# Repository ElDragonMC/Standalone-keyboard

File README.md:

# Standalone keyboard
This is my project for third week Half Life, a keyboard powered with a ESP32 connected to a power bank that uses a speaker to play 3 diferent sounds (acoustic, electric and organ). That's what makes it standalone!

I enjoyed very much making this project (specialy the PCB). For me, the most difficult part, was making the code so it can properly function.

# PCB Schematic:

# Some PCB Renders:

Front:

Back:

# Bill Of Materials

| Item | Qty | Supplier | Cost/item | Total Cost | link |
| --- | --- | --- | --- | --- | --- |
| PCB | 1 | JLCPCB | $5.00 | $5.00 | [JLCPCB](https://jlcpcb.com/) |
| Speaker | 1 | ElectroHobby | $1.66 | $1.66 | [ElectroHobby](https://www.electrohobby.es/sonido/305-altavoz-2w-28mm.html) |
| Amplifier | 1 | ElectroHobby | $2.78 | $2.78 | [ElectroHobby](https://www.electrohobby.es/sonido/984-max98357-amplificador-i2s.html) |
| Rotary Encoder | 1 | ElectroHobby | $1.28 | $1.28 | [ElectroHobby](https://www.electrohobby.es/entradassalidas/454-modulo-encoder-ky-040.html) |
| ESP32-S3-Zero | 1 | ElectroHobby | $5.00 | $5.00 | [ElectroHobby](https://www.electrohobby.es/esp32/957-esp32-c3-zero.html) |
| MPR121 | 1 | Amazon ES | $7.80 | $7.80 | [Amazon ES](	https://amzn.eu/d/0ajJMPyk) |
| 40x Blue Pin Header | ElectroHobby | $0.33 | $0.33 | [ElectroHobby](https://www.electrohobby.es/tiras-de-pines/236-tira-40-pin-macho-azul.html) |
| **Estimated total shipping** | **1** | — | — | **$3.49** | — |
| **Total Cost** | **1** | — | — | **$27.34** | — |

# Desing Process

I designed the PCB with KiCad (the only PCB design software i know how to use) following some parts from the starter guide to have a base idea. I wanted to make a case for it but i think it will look cooler to have it raw. A sleek black PCB will look very cool.

# How To Assemble

1. First grab the PCB and verify if it's clean and well-made.
2. Grab the ESP32, the MPR121 and the Amplifier and solder the pin headers. For the ESP32 it's two 9 pin header, for the MPR121, it's a 6 pin header and a 12 pin header and finaly for the amplifier it's two one pin header and a 7 pin header.
3. Weld the ESP32, the MPR121, the Amplifier, the JST connector for the speaker, the three switches and the rotary encoder to the PCB
4. There's two parts on the pack of the JST connector. One it's welded on the PCB. The other you have to solder it to the who cables of the speaker. **MAKE SURE THE RED WIRE GOES TO THE UPPER PART OF THE JST CONNECTOR**
5. Hot glue the speaker to the PCB

# How to upload the firmware

1. Open the Arduino IDE
2. Open **File → Preferences**. In **Additional Boards Manager URLs**, add:

   ~~~text
   https://espressif.github.io/arduino-esp32/package_esp32_index.json
   ~~~

3. Open **Tools → Board → Boards Manager**, search for esp32, and install **esp32 by Espressif Systems**.
4. Under **Tools → Board → esp32**, select **Waveshare ESP32-S3-Zero**.
5. Open **Sketch → Include Library → Manage Libraries**. Install this library:

   - Adafruit MPR121

   If Arduino asks to install dependencies, choose **Install All**.

6. Connect the ESP32 to the computer.
7. Open keyboard_code.ino and click Arduino's arrow-shaped **Upload** button to upload the firmware to the board.

# Controls

| Control (from left to right) | What it does |
| --- | --- |
| First button | Plays with the Acoustic sound |
| Second button | Plays with the Electric sound |
| Third button | Plays with the Organ sound |
| Rotary encoder | Control the volume |

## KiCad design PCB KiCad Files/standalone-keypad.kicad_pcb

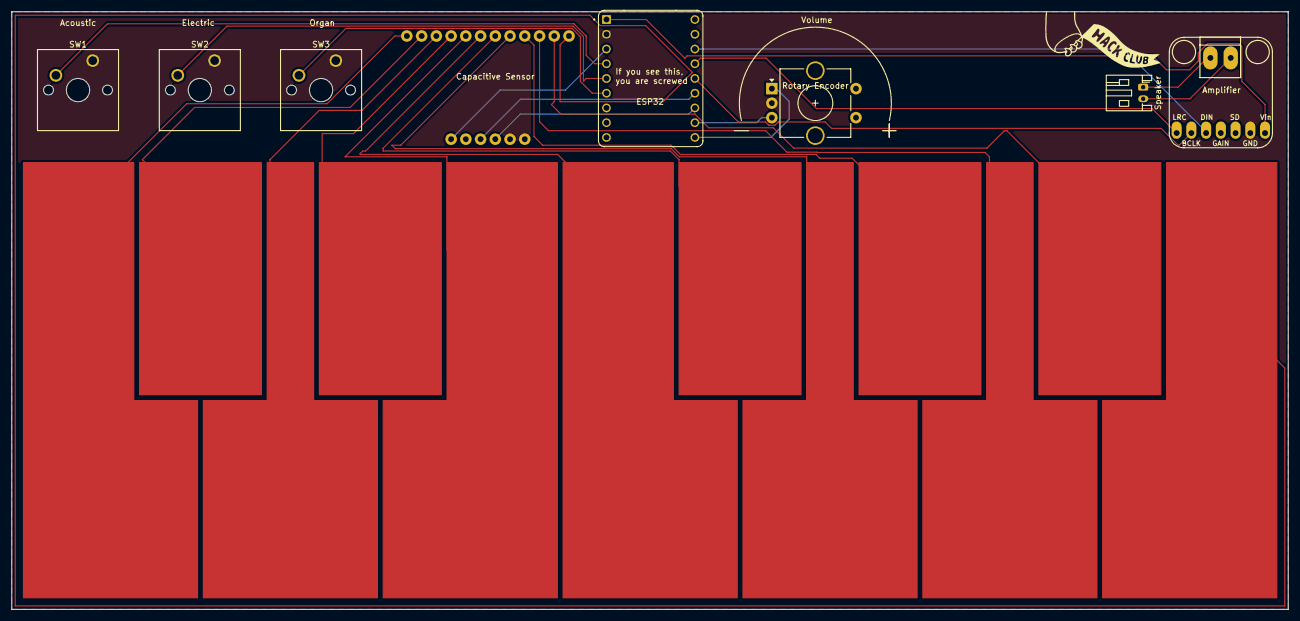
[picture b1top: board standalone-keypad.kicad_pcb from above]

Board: 2 copper layers, 220.0 x 103.0 mm, 9 parts (0 on the bottom side), 27 nets.

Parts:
Amplifier: adafruit-MAX98357 Amplifier; adafruit-MAX98357
Capacitive Sensor: MPR121QR2 Capacitive Sensor; MPR121
ESP32: Capacitive keys; Keyboard
Rotary Encoder: Volume Knob; RotaryEncoder_Alps_EC11E-Switch_Vertical_H20mm_CircularMoun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
SW1: Acoustic sound; SW_Cherry_MX_1.00u_PCB
SW2: Electric sound; SW_Cherry_MX_1.00u_PCB
SW3: Organ sound; SW_Cherry_MX_1.00u_PCB
Speaker: Speaker; JST_PH_S2B-PH-K_1x02_P2.00mm_Horizontal
U1: ESP32-S3-ZERO; MODULE_ESP32-S3-ZERO

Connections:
+3V3: Capacitive Sensor.1 (~IRQ), U1.3V3 (3V3(OUT))
+5V: Amplifier.1 (Vin), U1.5V
/ACOUSTIC: SW1.2, U1.1 (GP1)
/AUDIO DATA: Amplifier.5 (DIN), U1.13 (GP13)
/AUDIO TIMING 1: Amplifier.6 (BCLK), U1.11 (GP11)
/AUDIO TIMING 2: Amplifier.7 (LRC), U1.12 (GP12)
/DO: Capacitive Sensor.7 (REXT), ESP32.1
/DO#: Capacitive Sensor.8 (ELE0), ESP32.2
/ELECTRIC: SW2.2, U1.2 (GP2)
/FA: Capacitive Sensor.12 (LED0/ELE4), ESP32.6
/FA#: Capacitive Sensor.13 (LED1/ELE5), ESP32.7
/LA: Capacitive Sensor.16 (LED4/ELE8), ESP32.10
/LA#: Capacitive Sensor.17 (LED5/ELE9), ESP32.11
/MI: Capacitive Sensor.11 (ELE3), ESP32.5
/ORGAN: SW3.2, U1.3 (GP3)
/RE: Capacitive Sensor.9 (ELE1), ESP32.3
/RE#: Capacitive Sensor.10 (ELE2), ESP32.4
/SI: Capacitive Sensor.18 (LED6/ELE10), ESP32.12
/SOL: Capacitive Sensor.14 (LED2/ELE6), ESP32.8
/SOL#: Capacitive Sensor.15 (LED3/ELE7), ESP32.9
/SPEAKER +: Amplifier.8 (OUTP), Speaker.1
/SPEAKER -: Amplifier.9 (OUTN), Speaker.2
/TOUCH CLOCK: Capacitive Sensor.3 (SDA), U1.10 (GP10)
/TOUCH DATA: Capacitive Sensor.4 (ADDR), U1.9 (GP9)
/VOLUME 1: Rotary Encoder.A, U1.7 (GP7)
/VOLUME 2: Rotary Encoder.B, U1.8 (GP8)
GND: Amplifier.2 (GND), Capacitive Sensor.5 (VREG), Capacitive Sensor.6 (VSS), Rotary Encoder.C, SW1.1, SW2.1, SW3.1, U1.GND
